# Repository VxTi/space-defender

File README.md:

# 🎮 TI Game Controller

De opdracht van Technische Informatica (TI) bestaat uit het ontwikkelen van een niet al te ingewikkelde browser-spel welke je gaat aansturen met je zelf gemaakt controller!

Aan dit project werk je in een tweetal, waarbij je onze Gitlab omgeving gebruikt
voor het bijhouden van je code, documentatie en planning.

## 📁 Bestandsstructuur

In deze repository krijgen jullie een structuur aan bestanden, hierbij mag je zelf wijzigingen maken in de bestanden die je nodig hebt.
De structuur is als volgt:

- `docs`: Hierin kan je de documentatie kwijt voor jouw project. Hiervan wordt een website gegenereerd die je kan vinden onder 'Pages' (Deploy > Pages).
- `teamdocumentatie`: In deze map kan je (markdown!) documenten kwijt die gaan over de samenwerking in het team, wat je niet op je gegenereerde website wilt hebben.
- `arduino`: Hierin kan je de code kwijt voor jouw project wat te maken heeft met je embedded systeem, code geschreven in Arduino.
- `web`: Hierin kan je de code kwijt voor jouw project wat te maken heeft met de webapplicatie, bijvoorbeeld HTML, CSS en Javascript.
- `server`: Hier kan je je server applicatie kwijt die gaat zorgen voor de verbinding tussen jouw embedded systeem, web-applicatie en database.

## 📝 Opdracht

De opdracht vinden jullie in de map `docs` onder `opdracht.md`. Hierin staat de opdracht beschreven en de eisen waaraan je moet voldoen. Beter is om de opdracht te bekijken via `Deploy` > `Pages`, en vervolgens te navigeren naar de opdracht.

Daarnaast vind je in dit Gitlab-project:

- User Stories (Plan > Issues)
- Learning Stories (Plan > Issues)
- Scrum Board (Plan > Boards)
- Sprints (Plan > Milestones)

## 📚 Documentatie

Naast het schrijven van commentaar in je code ga je ook aan de slag met het schrijven van documentatie. Dit doe je door in de map `docs` een Markdown bestand aan te maken. Dit bestand wordt automatisch omgezet naar een website die je kan vinden onder 'Pages' (Deploy > Pages).

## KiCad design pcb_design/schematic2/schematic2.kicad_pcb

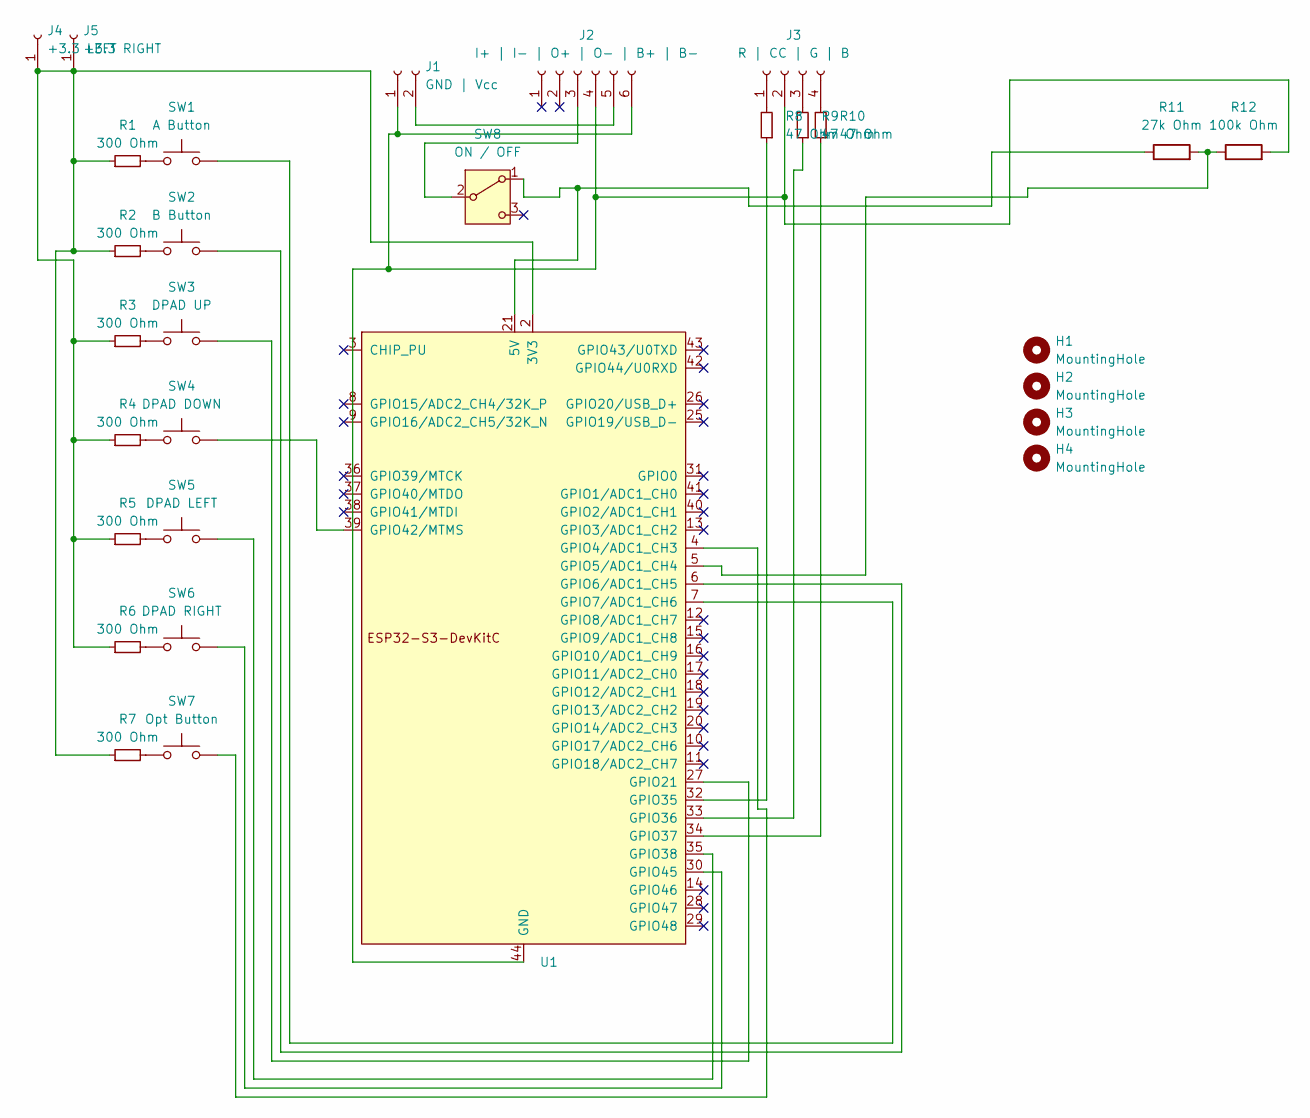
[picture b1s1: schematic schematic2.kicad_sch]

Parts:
H1, H2, H3, H4: MountingHole; MountingHole_2.5mm_Pad
J1: GND | Vcc; SolderWire-1.5sqmm_1x02_P7.8mm_D1.7mm_OD3.9mm
J2: I+ | I- | O+ | O- | B+ | B-; TP4056-Module
J3: R | CC | G | B; LED_D5.0mm-4_RGB
J4: +3.3 LEFT; MountingHole_2.5mm_Pad
J5: +3.3 RIGHT; MountingHole_2.5mm_Pad
R1, R2, R3, R4, R5, R6, R7: 300 Ohm; R_Axial_DIN0207_L6.3mm_D2.5mm_P10.16mm_Horizontal
R8, R9, R10: 47 Ohm; R_Axial_DIN0207_L6.3mm_D2.5mm_P10.16mm_Horizontal
R11: 27k Ohm; R_Axial_DIN0207_L6.3mm_D2.5mm_P10.16mm_Horizontal
R12: 100k Ohm; R_Axial_DIN0207_L6.3mm_D2.5mm_P10.16mm_Horizontal
SW1: A Button; SW_PUSH_6mm
SW2: B Button; SW_PUSH_6mm
SW3: DPAD UP; SW_PUSH_6mm
SW4: DPAD DOWN; SW_PUSH_6mm
SW5: DPAD LEFT; SW_PUSH_6mm
SW6: DPAD RIGHT; SW_PUSH_6mm
SW7: Opt Button; SW_PUSH_6mm
SW8: ON / OFF; PinSocket_1x03_P2.54mm_Vertical
U1: ESP32; ESP32S3_Dev_Module

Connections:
unnamed: J1.1, J2.4, J2.6, J3.2, R12.2, U1.22 (GND), U1.23 (GND), U1.24 (GND), U1.44 (GND)
unnamed: J1.2, J2.5
unnamed: J2.3, SW8.2 (B)
unnamed: J3.1, R8.2
unnamed: J3.3, R9.2
unnamed: J3.4, R10.2
unnamed: J4.1, J5.1, R1.1, R2.1, R3.1, R4.1, R5.1, R6.1, R7.1, U1.1 (3V3), U1.2 (3V3)
unnamed: R1.2, SW1.1
unnamed: R2.2, SW2.1
unnamed: R3.2, SW3.1
unnamed: R4.2, SW4.1
unnamed: R5.2, SW5.1
unnamed: R6.2, SW6.1
unnamed: R7.2, SW7.1
unnamed: R11.1, SW8.1 (A), U1.21 (5V)
unnamed: SW7.2, U1.4 (GPIO4/ADC1_CH3)
unnamed: R11.2, R12.1, U1.5 (GPIO5/ADC1_CH4)
unnamed: SW2.2, U1.6 (GPIO6/ADC1_CH5)
unnamed: SW1.2, U1.7 (GPIO7/ADC1_CH6)
unnamed: SW3.2, U1.27 (GPIO21)
unnamed: R8.1, U1.32 (GPIO35)
unnamed: R9.1, U1.33 (GPIO36)
unnamed: R10.1, U1.34 (GPIO37)
unnamed: SW5.2, U1.35 (GPIO38)
unnamed: SW4.2, U1.39 (GPIO42/MTMS)
unnamed: SW6.2, U1.30 (GPIO45)

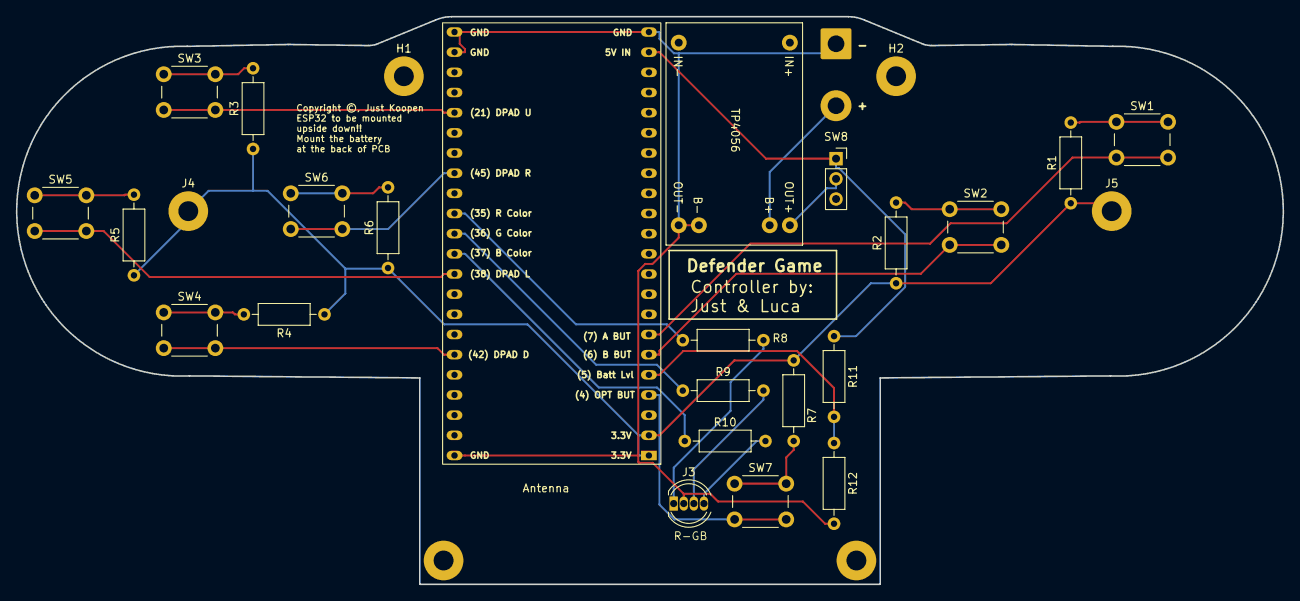
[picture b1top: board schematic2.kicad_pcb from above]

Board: 2 copper layers, 159.5 x 71.5 mm, 30 parts (0 on the bottom side), 26 nets.

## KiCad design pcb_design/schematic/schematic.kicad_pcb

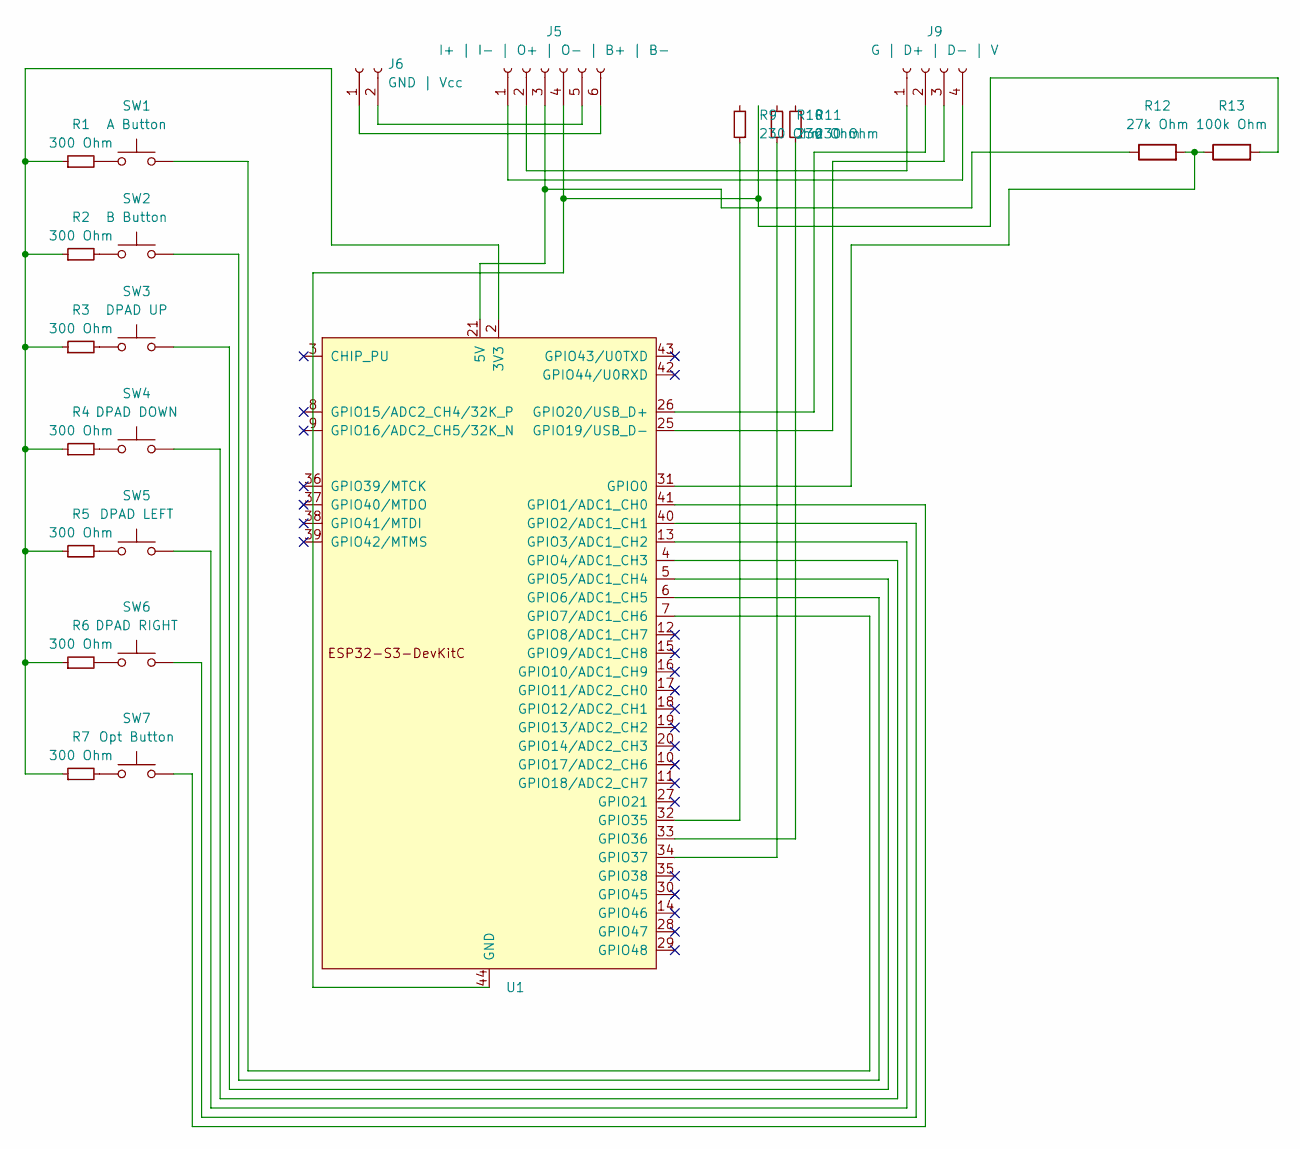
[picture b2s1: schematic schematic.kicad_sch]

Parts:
J5: I+ | I- | O+ | O- | B+ | B-; TP4056-Module
J6: GND | Vcc; SolderWire-2sqmm_1x02_P7.8mm_D2mm_OD3.9mm
J9: G | D+ | D- | V; PinHeader_1x04_P2.54mm_Vertical
R1, R2, R3, R4, R5, R6, R7: 300 Ohm; R_Axial_DIN0207_L6.3mm_D2.5mm_P10.16mm_Horizontal
R9, R10, R11: 230 Ohm; R_Axial_DIN0207_L6.3mm_D2.5mm_P10.16mm_Horizontal
R12: 27k Ohm; R_Axial_DIN0207_L6.3mm_D2.5mm_P10.16mm_Horizontal
R13: 100k Ohm; R_Axial_DIN0207_L6.3mm_D2.5mm_P10.16mm_Horizontal
SW1: A Button; SW_PUSH_6mm
SW2: B Button; SW_PUSH_6mm
SW3: DPAD UP; SW_PUSH_6mm
SW4: DPAD DOWN; SW_PUSH_6mm
SW5: DPAD LEFT; SW_PUSH_6mm
SW6: DPAD RIGHT; SW_PUSH_6mm
SW7: Opt Button; SW_PUSH_6mm
U1: ESP32; ESP32-S3-DevKitC

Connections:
unnamed: J5.1, J9.4
unnamed: J5.2, J9.1
unnamed: J5.3, R12.1, U1.21 (5V)
unnamed: J5.4, R13.2, U1.22 (GND), U1.23 (GND), U1.24 (GND), U1.44 (GND)
unnamed: J5.5, J6.2
unnamed: J5.6, J6.1
unnamed: J9.2, U1.26 (GPIO20/USB_D+)
unnamed: J9.3, U1.25 (GPIO19/USB_D-)
unnamed: R1.1, R2.1, R3.1, R4.1, R5.1, R6.1, R7.1, U1.1 (3V3), U1.2 (3V3)
unnamed: R1.2, SW1.1
unnamed: R2.2, SW2.1
unnamed: R3.2, SW3.1
unnamed: R4.2, SW4.1
unnamed: R5.2, SW5.1
unnamed: R6.2, SW6.1
unnamed: R7.2, SW7.1
unnamed: R12.2, R13.1, U1.31 (GPIO0)
unnamed: SW7.2, U1.41 (GPIO1/ADC1_CH0)
unnamed: SW6.2, U1.40 (GPIO2/ADC1_CH1)
unnamed: SW5.2, U1.13 (GPIO3/ADC1_CH2)
unnamed: SW4.2, U1.4 (GPIO4/ADC1_CH3)
unnamed: SW3.2, U1.5 (GPIO5/ADC1_CH4)
unnamed: SW2.2, U1.6 (GPIO6/ADC1_CH5)
unnamed: SW1.2, U1.7 (GPIO7/ADC1_CH6)
unnamed: R9.1, U1.32 (GPIO35)
unnamed: R11.1, U1.33 (GPIO36)
unnamed: R10.1, U1.34 (GPIO37)

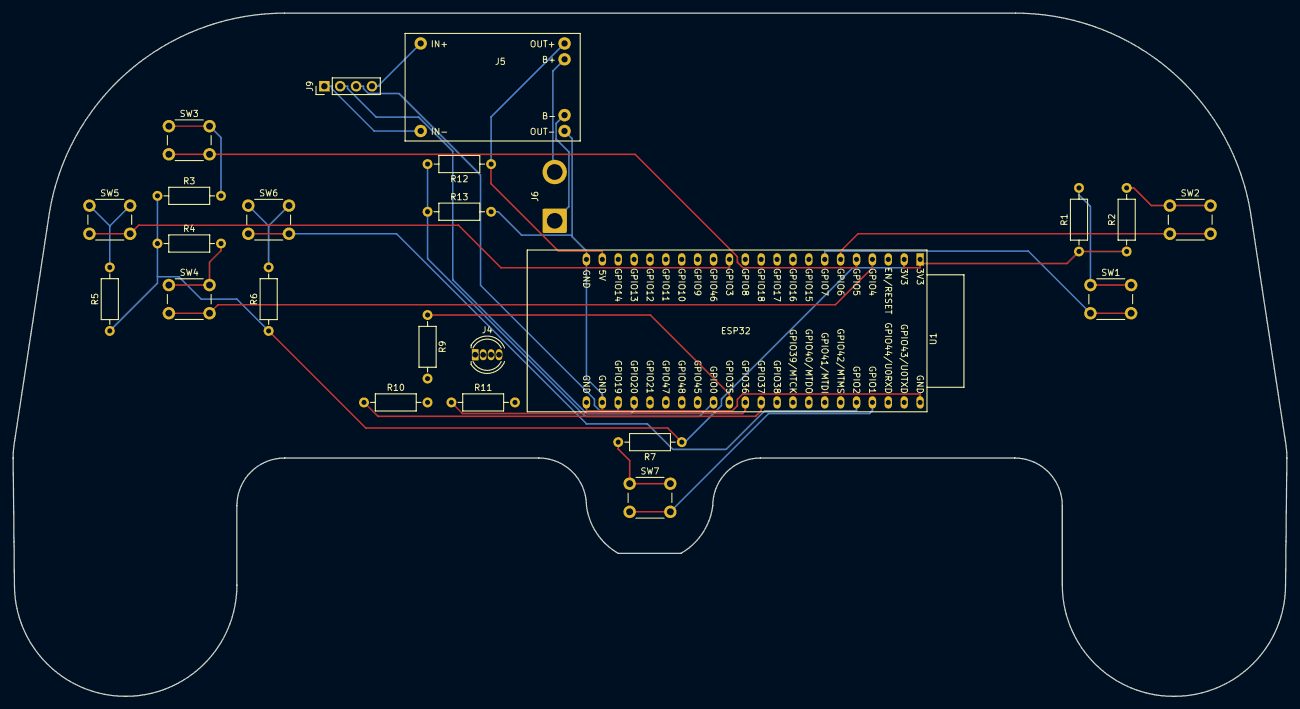
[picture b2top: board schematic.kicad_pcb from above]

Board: 2 copper layers, 203.6 x 109.2 mm, 24 parts (0 on the bottom side), 27 nets.

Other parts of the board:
J4: R | CC | B | G; LED_D5.0mm-4_RGB

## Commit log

2023-11-21 Project-bestanden van TI - Game Controller gekopieerd
2023-11-21 Added submodule mdocotion
2023-11-21 Added BoundingBox class
2023-11-21 Added collision detection for players
2023-11-21 Updated collision detection
2023-11-21 Added gitignore
2023-11-21 Added player image
2023-11-21 Added ino file and updated gitignore
2023-11-21 Wrote serial code and pin readings
2023-11-21 Separated Entity, AABB and Environment into separate javascript files, added comments to controller.ino
2023-11-22 Reverted file separation
2023-11-22 Improved player movement checks
2023-11-22 Added bluetooth support (?)
2023-11-22 Made changes to bluetooth protocol
2023-11-22 Added BT example
2023-11-22 Code for sending BLE data added (?)
2023-11-22 Added Bluetooth class for multiple controller support
2023-11-22 Added code for reading and sending button data
2023-11-22 Changed controller output from JSON to single byte
2023-11-22 Changed controller output from JSON to single byte (2)
2023-11-23 Fixed non-scalar error
2023-11-23 Changed BT Controller functionality
2023-11-23 Added bluetooth functionality to the website
2023-11-23 Initial commit for binary char set
2023-11-23 Separated classes in files, improved BT functionality
2023-11-23 Changed pin readout method to char array
2023-11-23 Added changes to game mechanics
2023-11-24 Returned bitshifting
2023-11-24 Changed notify call
2023-11-24 Made BT Changes
2023-11-24 Changed User input functionality for controller
2023-11-24 Added debug mode
2023-11-24 Further work on debugging
2023-11-24 Added Joystick functionality
2023-11-24 Changed map visibility
2023-11-24 Organised files
2023-11-24 Fixed debug mode
2023-11-27 Added NodeJS server functionality
2023-11-27 Added comments
2023-11-28 added changes
2023-11-28 Added Resource class for animation compatibility
2023-11-28 Reverted joystick functionality, added back regular input buttons
2023-11-28 Cleaned up game.js, moved AABB to utilities.js
2023-11-28 Added blocksprite
2023-11-28 Added select player functionality
2023-11-28 Added filters to BLE Service
2023-11-28 Added resource loading changes
2023-11-28 Added collision detection back !!
2023-11-28 Added random UUIDs
2023-11-29 added useless documents
2023-11-29 Removed random UUID, added static UUID
2023-11-29 fucked around with arduino.ino and found out
2023-11-29 Changed controller input code
2023-11-29 Added useless document
2023-11-29 Added feedback and images
2023-11-29 Added manual
2023-11-29 Updated graphics (minecraft edition)
2023-11-29 Added minecraft font and other textures
2023-11-30 Added more resources, added skybox, added moon and animations
2023-11-30 Sorted files, added pause, play and settings button
2023-11-30 Added minor changes
2023-11-30 Fixed pipeline??
2023-11-30 Made changes to collision detection, world generation. Changed settings icon
2023-11-30 Added double jump and block highlighting
2023-11-30 Updated Y screen scrolling
2023-11-30 Changed textures
2023-11-30 Added gold
2023-11-30 Added healthbar
2023-11-30 Added healthbar functionality (fall damage)
2023-12-01 Optimized code, added multiple entity support
2023-12-01 Added entity pushing
2023-12-01 Added moving animation
2023-12-01 Fixed bug where half hearts weren't showing, added coal
2023-12-01 Pipeline fixed (?) and regeneration added
2023-12-01 Pipeline fixed (2)
2023-12-01 Pipeline fixed (999)
2023-12-01 Added begin of documentation for game functionality
2023-12-01 Added hostile entities (Test?)
2023-12-01 Added Serial coms to website and esp32
2023-12-01 Changed movement code
2023-12-01 Commented out serial comms temp
2023-12-01 Commented out stuff in game
2023-12-01 PowerPoint
2023-12-01 Changed bluetooth functionality
2023-12-03 Added a very scary wizard :o
2023-12-03 Added better healthbar (for higher health counts), and a shitty version of wizard balls
2023-12-03 added fireball texture
2023-12-05 Added mySQL
2023-12-05 Added libraries.
2023-12-05 Added mySQL to server.js
2023-12-05 Added query login
2023-12-06 Added battery readings and db connection
2023-12-06 Added data logging to console
2023-12-06 Added database functionality to server.js
2023-12-07 Fixed dbconnection. Ook heeft Nick feedback gegeven.
2023-12-08 Fixed DB connection (again)
2023-12-08 Separated all script files
2023-12-08 Added OPT button functionality
2023-12-08 Added API
2023-12-08 Added POST requests to API
2023-12-08 Added example website, added CORS to server
2023-12-11 Fixed scriptloader now chronologically loading scripts, added more private fields to please teachers
2023-12-11 Made changes to pause menu, added main menu
2023-12-12 Changed some fields to private and added getter and setters
2023-12-12 Changed menu functionality
2023-12-12 Added API calls for getting, posting and creating userdata in the DB
2023-12-12 Added mySQL formatting and placeholders to prevent 'malicious SQL injection'
2023-12-13 Added DELETE request and API docs
2023-12-13 Fixed doc????
2023-12-13 Updated .pages
2023-12-13 Added admonitions to API docs
2023-12-13 Added more admontations
2023-12-13 Added more comments to api.js
2023-12-13 Added blank spaces and an example
2023-12-13 Fixed pipeline again???
2023-12-13 Changed styles
2023-12-13 Added new API calls: Highscore and most coins
2023-12-13 Fixed pipeline again???????
2023-12-13 pipeline check
2023-12-13 Added HTTP status codes to docs
2023-12-13 Changed headings
2023-12-13 Fixed pipeline maybe?
2023-12-13 Pipeline??
2023-12-13 Edited mkdocs.yml
2023-12-13 Changed readme
2023-12-13 Added . to apidocs
2023-12-13 Rewinded changes to gitlab-ci and mkdocs.yml
2023-12-13 Added UML Class documentation
2023-12-13 Possibly finaly fixed pipeline? And added loadingscreen HTML
2023-12-13 Added loading screen
2023-12-13 Added leaderboard functions to the API, and updated docs
2023-12-14 Added leaderboards retrieving
2023-12-14 Hopefully fixed issues with docs now
2023-12-14 Changed api logging
2023-12-14 Fixed pipeline maybe??
2023-12-14 Changed UI features
2023-12-15 Added API key authentication
2023-12-15 Added rate limiting
2023-12-15 Added formatting
2023-12-15 Changed API features
2023-12-15 Removed certain API requests and replaced it with a generic one
2023-12-15 Added API docs for api keys and rate limiting
2023-12-15 Updated documentation
2023-12-15 Added key checking function, optimizing code
2023-12-16 Added server.js for separate hosting
2023-12-18 Added controller menu selecting
2023-12-18 Added menu intractability from controller
2023-12-18 Added quad-tree class for future map optimization
2023-12-19 Documentatie (feedback) aangepast
2023-12-19 Updated docs
2023-12-19 Changes?
2023-12-19 Changed terrain, added quad-trees into mesh generation
2023-12-19 Added comparisons
2023-12-19 Complete overhaul for API
2023-12-19 Finished overhauling API with new functions in seperate DB tables
2023-12-20 Complete overhaul for docs
2023-12-20 Changed API docs with more admontations
2023-12-20 Fixed type errors
2023-12-20 Added delete user function
2023-12-20 Added user checking
2023-12-20 Added todo for api
2023-12-20 Remade entire game, making Space Defender now.
2023-12-20 Fixed error when checking length of undefined values
2023-12-21 Added inner map and changed textures
2023-12-21 Added bullet collision and death animation and score system
2023-12-21 Adjusted death animations
2023-12-21 Editted taken.md
2023-12-23 Fixed rocket collision detection
2023-12-23 Added shooting cooldown
2023-12-24 Optimized code
2023-12-25 Optimized code again
2023-12-25 Added database checks and score updating in-game, and optimized
2023-12-26 Added highscore updating and loading
2023-12-27 Changed movement code and made optimizations
2023-12-28 Added health element, added enemy ship, fixed particle system, added extra JSDocs
2023-12-29 Added special blast
2023-12-30 Changed particle system, updated graphics
2023-12-30 Updated shooting animation
2024-01-01 Changed spaceship acceleration and rocket visibility
2024-01-06 Added real battery checking
2024-01-07 Made slight adaptions
2024-01-07 Changed battery voltages
2024-01-07 Changed battery readings again
2024-01-10 Added PCB schematics and layout design files
2024-01-10 Added feedback
2024-01-10 Added begin of new entity for higher waves
2024-01-10 PCB schematic files
2024-01-10 Update schematic2.kicad_sch file
2024-01-12 Organized code, made changes to evolved alien and UI
2024-01-12 Remove lock files
2024-01-12 Added saving of statistics
2024-01-12 Made changes to statistics
2024-01-12 Added switch to PCB design and fixed battery readings
2024-01-12 Updated API docs
2024-01-15 Added new library sketch
2024-01-16 Reverted arduino code to a previous (working) version
2024-01-16 Reverted arduino.ino
2024-01-16 Updated feedback
2024-01-16 Improved documentation
2024-01-16 Added soundpack
2024-01-16 Soundpack
2024-01-16 No idea
2024-01-16 Added audioplayer
2024-01-16 Changed death sound
2024-01-16 Added hit2
2024-01-16 Added sound effects
2024-01-16 Add global volume control and continuous sound playback
2024-01-16 Updated JSDocs
2024-01-16 Added p5 sound library
2024-01-16 Added code documentation and markdown generator
2024-01-16 Updated pages for deployment
2024-01-16 Fixed deploy page
2024-01-17 Updated arduino code
2024-01-17 Added wave system and made audio changes
2024-01-17 kicad files
2024-01-17 Added flying sound
2024-01-18 Changed broadcasting system and fixed wave system
2024-01-19 Added virtual keyboard functionality
2024-01-19 Added extra sounds and made optimizations
2024-01-19 more kicad files
2024-01-19 Changed pins
2024-01-20 Update documentation
2024-01-20 Updated takenlijst
2024-01-20 Update navigation structure in .pages file
2024-01-21 More documentation
2024-01-21 typo
2024-01-21 Last commit for docs today
2024-01-22 Added score page to see one's statistics and scores on a simple page
2024-01-22 Update navigation and add PCB result image
2024-01-23 Added circuit.md
2024-01-23 Updated pages for new page
2024-01-23 Remove material-extensions plugin and add pymdownx.emoji and pymdownx.highlight plugins
2024-01-23 Fix typo and add new button option
2024-01-23 Updated component list
2024-01-23 Updated arduino.ino, made changes to game functionality
2024-01-23 Transferred BLEGamepad.ino content to arduino.ino, deleted BLEGamepad.ino
2024-01-23 Fixed typo
2024-01-23 Added more icons
2024-01-23 added a scary sound
2024-01-23 Added sources to bronvermelding
2024-01-23 fixed scary sound being too scary
2024-01-24 Updated taken.md
2024-01-24 LAst docs
2024-01-24 Add RGB LED initialization and delay in setup() function
2024-01-24 Fixed API allowing invalid keys
2024-01-24 Added presentation
2024-01-24 Added recieved feedback to docs
2024-01-24 Updated UML diagrams
2024-01-24 Removed settings screen; unused
2024-01-24 Removed comments from arduino.ino
2024-01-24 Updated arduino.ino; Minimized code

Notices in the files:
pcb_design/schematic2/schematic2.kicad_pcb:
Copyright ©, Just Koopen
